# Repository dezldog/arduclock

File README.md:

# Instructions for `arduclock`

## Project Overview
This repository contains Arduino-based GPS clock projects with 7-segment displays. There are three main variants:
- `gps_clock_auto_timezone/`: GPS clock with automatic timezone detection based on GPS location.
- `gps_clock_tz_dst/`: GPS clock with manual DST and timezone selection via hardware pins.
- `original/`: Early version with manual UTC offset and DST toggle.

## Architecture & Key Files
- Each variant is a standalone `.ino` file, using similar hardware and libraries:
  - `Adafruit_LEDBackpack`, `Adafruit_GFX`, `Adafruit_GPS`, `SoftwareSerial`, `Wire`
- Hardware pins for timezone/DST selection are defined in each file (see `Config` namespace or `#define` macros).
- Display updates and GPS polling are managed via periodic intervals (see `DISPLAY_UPDATE_MS`, `TIMEZONE_CHECK_MS`, etc.).
- Timezone logic:
  - `gps_clock_auto_timezone`: Uses GPS coordinates to set timezone automatically.
  - `gps_clock_tz_dst`: Uses hardware pins for manual selection.
  - `original`: Uses fixed UTC offset and DST toggle.

## Developer Workflows
- **Build/Upload:**
  - Open the desired `.ino` file in the Arduino IDE or VS Code with Arduino extension.
  - Select the correct board and port, then upload as usual.
- **Debugging:**
  - Use `Serial.begin(115200)` for serial output (default baud rate).
  - Monitor serial output for GPS data and time updates.
- **Dependencies:**
  - Install required libraries via Arduino Library Manager:
    - Adafruit_LEDBackpack
    - Adafruit_GFX
    - Adafruit_GPS
    - SoftwareSerial
    - Wire (built-in)

## Project-Specific Patterns & Conventions
- **Pin Assignments:**
  - Timezone/DST selection pins are consistently assigned (see `Config` or macros).
  - GPS RX/TX pins: 8/7 (all variants).
- **Display Address:**
  - I2C address for display is `0x70`.
- **Time Format:**
  - 12-hour format by default (`TIME_24_HOUR = false`).
- **Serial Baud Rates:**
  - GPS: 9600
  - Serial Monitor: 115200
- **Update Intervals:**
  - Display: 100ms
  - Timezone check: 1s
  - Location check (auto mode): 30s

## Integration Points
- **External Services:**
  - No network/cloud integration; all logic is local to the Arduino.
- **PCB Files:**
  - Hardware design files in `original/` (`main_board.brd`, `.sch`).
  - Order PCBs via OSH Park (see README).

## Example: Adding a New Variant
- Copy an existing `.ino` file and update pin assignments, display logic, or timezone handling as needed.
- Follow the established pattern for hardware initialization and periodic updates.

## References
- Key files: `gps_clock_auto_timezone/gps_clock_auto_tz.ino`, `gps_clock_tz_dst/gps_clock_tz_dst.ino`, `original/clock_dst_tz.ino`
- Hardware: See `original/main_board.brd` and `.sch`
- README: Contains PCB ordering info and project links

---
**If any section is unclear or missing details, please provide feedback so this guide can be improved.**

View this project on [CADLAB.io](https://cadlab.io/node/898). 

# arduclock
PWBs available @ <a href="https://oshpark.com/shared_projects/jVSOJ3Xw"></img></a>

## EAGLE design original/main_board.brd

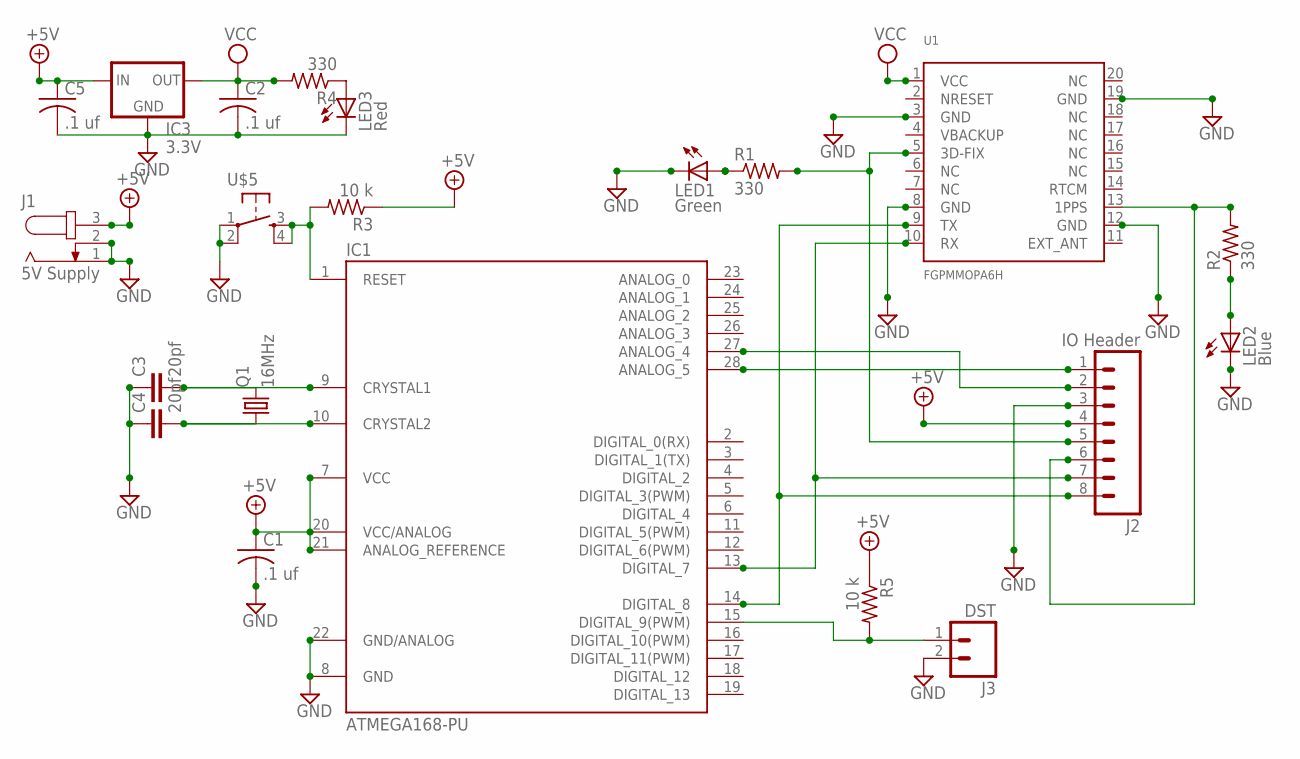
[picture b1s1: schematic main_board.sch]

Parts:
C1, C2, C5: .1 uf; C025-025X050
C3, C4: 20pf; C025-024X044
IC1: ATMEGA168-PU; DIL28-3
IC3: 3.3V; TO92
J1: 5V Supply; SPC4078
J2: IO Header; 1X08_ROUND
J3: DST; 1X02_LOCK
LED1: Green; LED3MM
LED2: Blue; LED3MM
LED3: Red; LED3MM
Q1: 16MHz; HC18U-V
R1, R2, R4: 330; 0204/5
R3, R5: 10 k; 0204/5
U1: FGPMMOPA6H
U$5: TACTILE-SWITCH-PTH; TAC-SWITCH-PTH

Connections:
+5V: C1.1, C5.1, IC1.7 (VCC), IC1.20 (VCC/ANALOG), IC1.21 (ANALOG_REFERENCE), IC3.2 (IN), J1.3, J2.4, R3.1, R5.1
DST: IC1.15 (DIGITAL_9(PWM)), J3.1, R5.2
GND: C1.2, C2.2, C3.1, C4.1, C5.2, IC1.8 (GND), IC1.22 (GND/ANALOG), IC3.1 (GND), J1.1, J1.2, J2.3, J3.2, LED1.K (C), LED2.K (C), LED3.K (C), U1.3 (GND), U1.8 (GND), U1.12 (GND), U1.19 (GND), U$5.1, U$5.2
unnamed: C4.2, IC1.10 (CRYSTAL2), Q1.1
unnamed: C3.2, IC1.9 (CRYSTAL1), Q1.2
unnamed: IC1.13 (DIGITAL_7), J2.7, U1.10 (RX)
unnamed: IC1.14 (DIGITAL_8), J2.8, U1.9 (TX)
unnamed: LED3.A, R4.1
unnamed: IC1.28 (ANALOG_5), J2.1
unnamed: IC1.1 (RESET), R3.2, U$5.3, U$5.4
unnamed: IC1.27 (ANALOG_4), J2.2
unnamed: J2.6, R2.2, U1.13 (1PPS)
unnamed: J2.5, R1.2, U1.5 (3D-FIX)
unnamed: LED1.A, R1.1
unnamed: LED2.A, R2.1
VCC: C2.1, IC3.3 (OUT), R4.2, U1.1 (VCC)

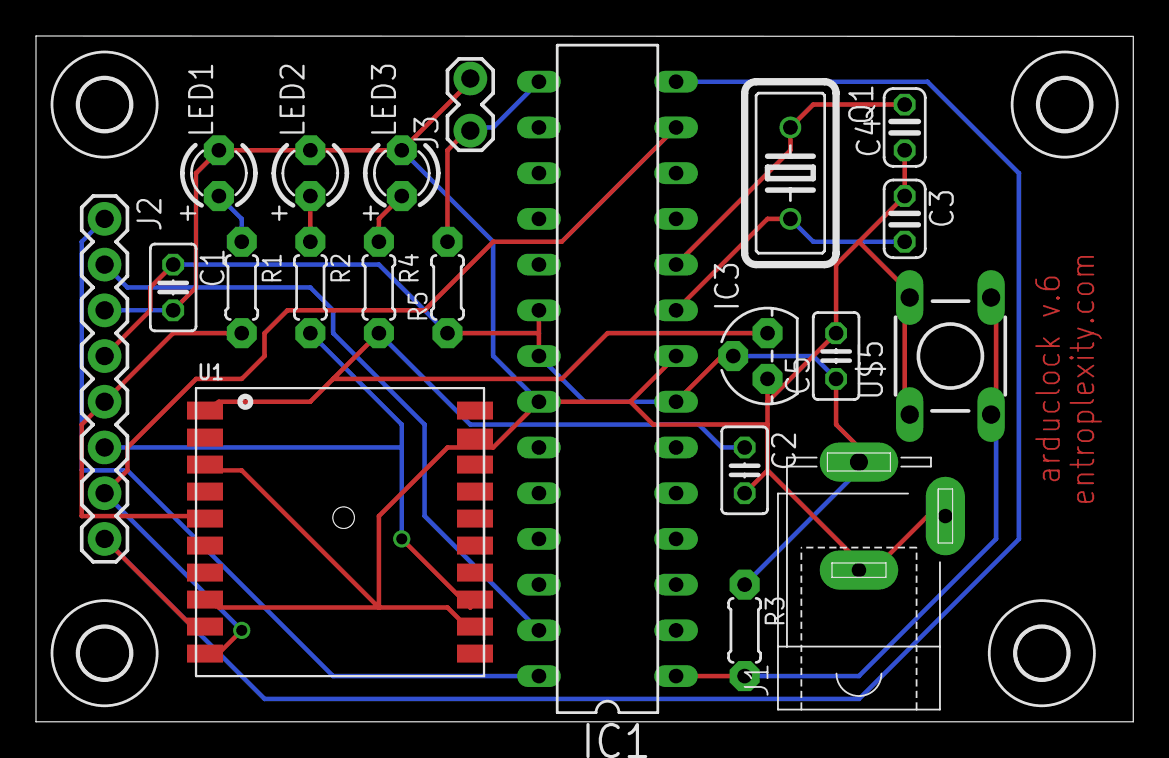
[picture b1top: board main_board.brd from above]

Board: 2 copper layers, 61.0 x 38.1 mm, 25 parts (0 on the bottom side), 16 nets.

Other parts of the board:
U$1, U$2, U$3, U$4: 2,8

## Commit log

2016-10-02 Kinda self-documented. Enough for a non-novice to build.
2018-04-18 Backlink to CADLAB.io has been added.
2025-07-05 Organizing and adding new code with time zone and dst switch
2025-07-05 more organizing
2025-07-09 new auto timezone code
2025-08-14 claude
2025-08-14 README
2025-08-14 Update README.md
    wording

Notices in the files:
parts and their libraries:
SparkFun-Connectors: Licensing: Creative Commons ShareAlike 4.0 International - https://creativecommons.org/licenses/by-sa/4.0
